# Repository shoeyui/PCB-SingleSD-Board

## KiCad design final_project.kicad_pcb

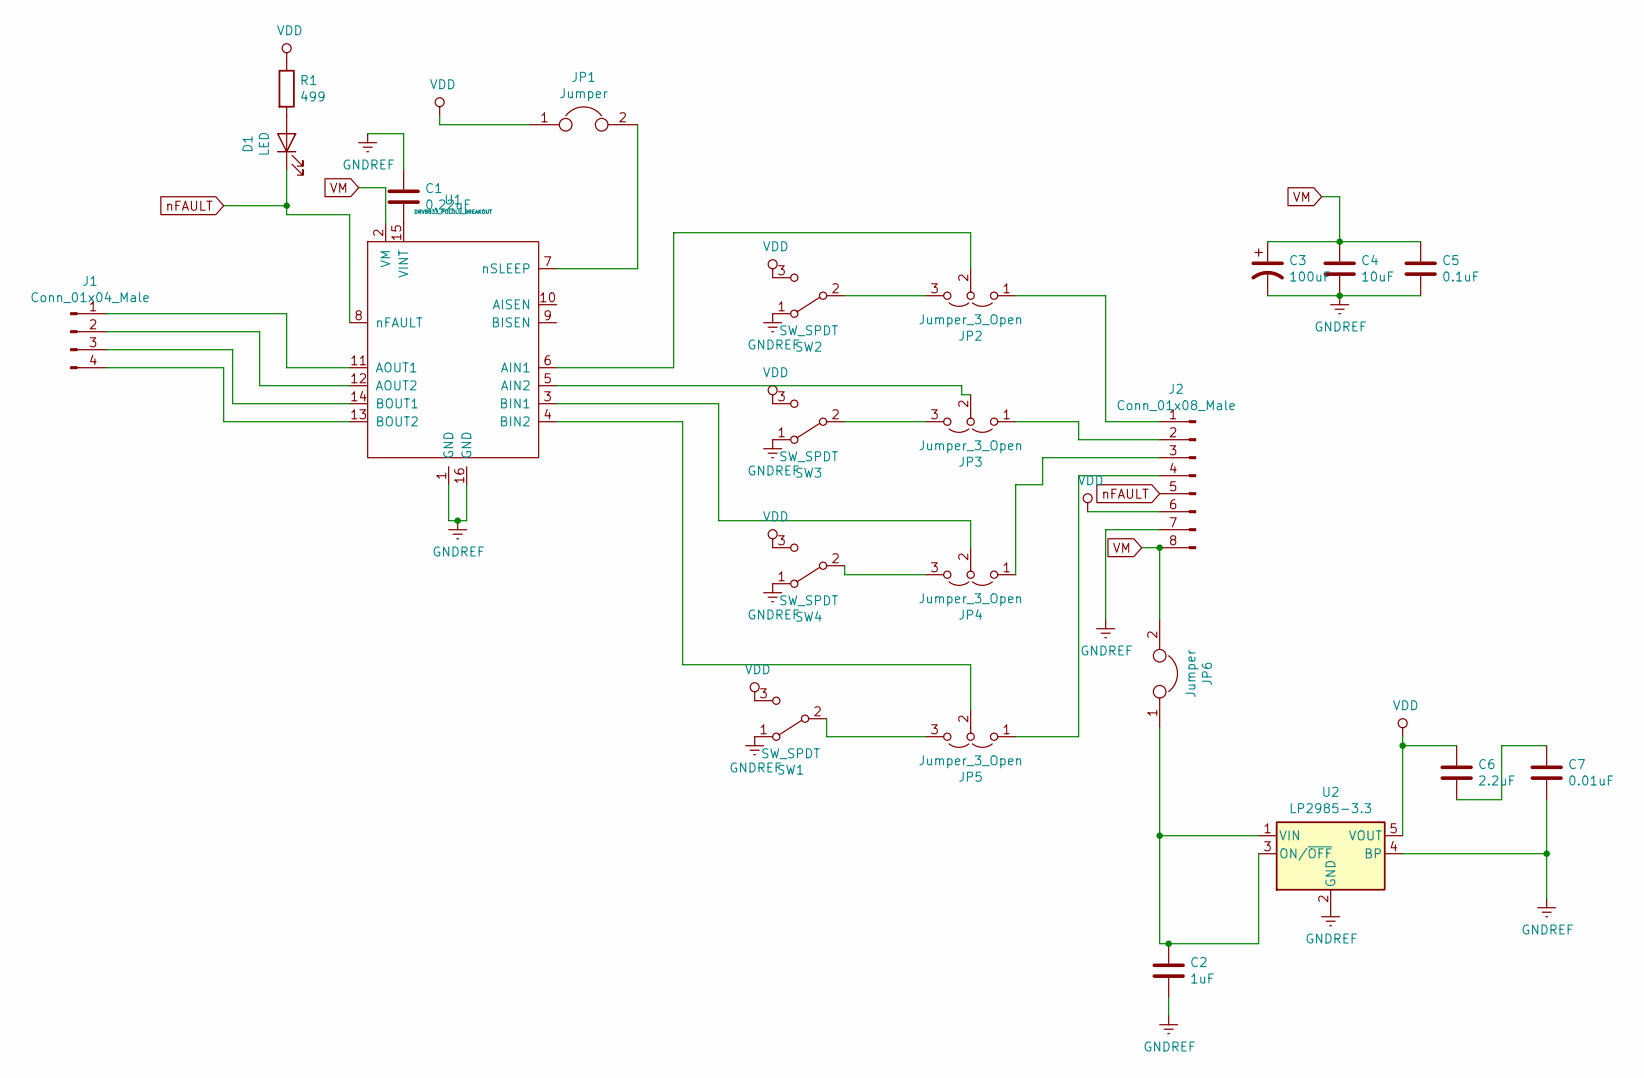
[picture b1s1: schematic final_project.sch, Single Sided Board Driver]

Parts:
C1: 0.22uF; CP_Radial_Tantal_D4.5mm_P2.50mm
C2: 1uF; CP_Radial_D4.0mm_P1.50mm
C3: 100uF; CP_Radial_D8.0mm_P5.00mm
C4: 10uF; CP_Radial_D4.0mm_P1.50mm
C5: 0.1uF; CP_Radial_Tantal_D4.5mm_P2.50mm
C6: 2.2uF; CP_Radial_Tantal_D4.5mm_P2.50mm
C7: 0.01uF; CP_Radial_Tantal_D4.5mm_P2.50mm
D1: LED; LED_D3.0mm
J1: Conn_01x04_Male; PinHeader_1x04_P1.00mm_Vertical
J2: Conn_01x08_Male; PinHeader_1x08_P1.00mm_Vertical
JP1, JP6: Jumper; PinHeader_1x02_P1.00mm_Vertical
JP2, JP3, JP4, JP5: Jumper_3_Open; PinHeader_1x03_P1.00mm_Vertical
R1: 499; R_Axial_DIN0207_L6.3mm_D2.5mm_P7.62mm_Horizontal
SW1, SW2, SW3, SW4: SW_SPDT; SW_CuK_OS102011MA1QN1_SPDT_Angled
U1: DRV8833_POLOLU_BREAKOUT
U2: LP2985-3.3; SOT-23-5

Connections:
GNDREF: C1.1, C2.2, C3.2, C4.2, C5.2, C7.2, J2.7, SW1.1 (A), SW2.1 (A), SW3.1 (A), SW4.1 (A), U1.1 (GND), U1.16 (GND), U2.2 (GND), U2.4 (BP)
unnamed: C1.2, U1.15 (VINT)
unnamed: C2.1, JP6.1, U2.1 (VIN), U2.3 (ON/~OFF~)
unnamed: C6.2, C7.1
unnamed: D1.2 (A), R1.2
unnamed: J1.1, U1.11 (AOUT1)
unnamed: J1.2, U1.12 (AOUT2)
unnamed: J1.3, U1.14 (BOUT1)
unnamed: J1.4, U1.13 (BOUT2)
unnamed: J2.1, JP2.1 (A)
unnamed: J2.2, JP3.1 (A)
unnamed: J2.3, JP4.1 (A)
unnamed: J2.4, JP5.1 (A)
unnamed: JP1.2, U1.7 (nSLEEP)
unnamed: JP2.2 (C), U1.6 (AIN1)
unnamed: JP2.3 (B), SW2.2 (B)
unnamed: JP3.2 (C), U1.5 (AIN2)
unnamed: JP3.3 (B), SW3.2 (B)
unnamed: JP4.2 (C), U1.3 (BIN1)
unnamed: JP4.3 (B), SW4.2 (B)
unnamed: JP5.2 (C), U1.4 (BIN2)
unnamed: JP5.3 (B), SW1.2 (B)
VDD: C6.1, J2.6, JP1.1, R1.1, SW1.3 (C), SW2.3 (C), SW3.3 (C), SW4.3 (C), U2.5 (VOUT)
VM: C3.1, C4.1, C5.1, J2.8, JP6.2, U1.2 (VM)
nFAULT: D1.1 (K), J2.5, U1.8 (nFAULT)

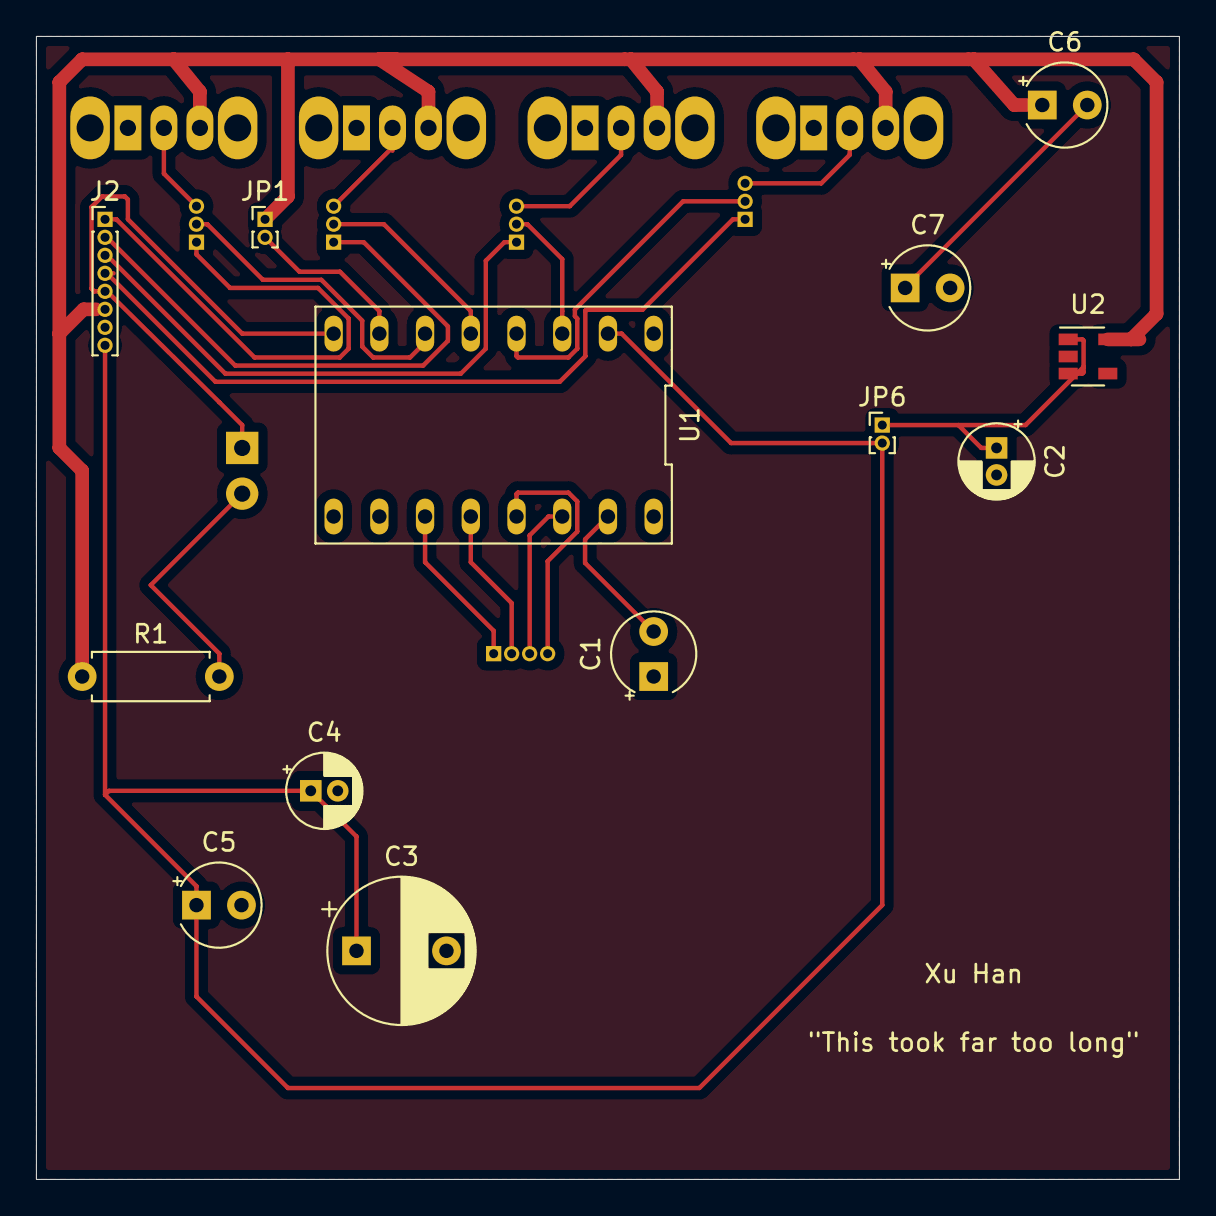
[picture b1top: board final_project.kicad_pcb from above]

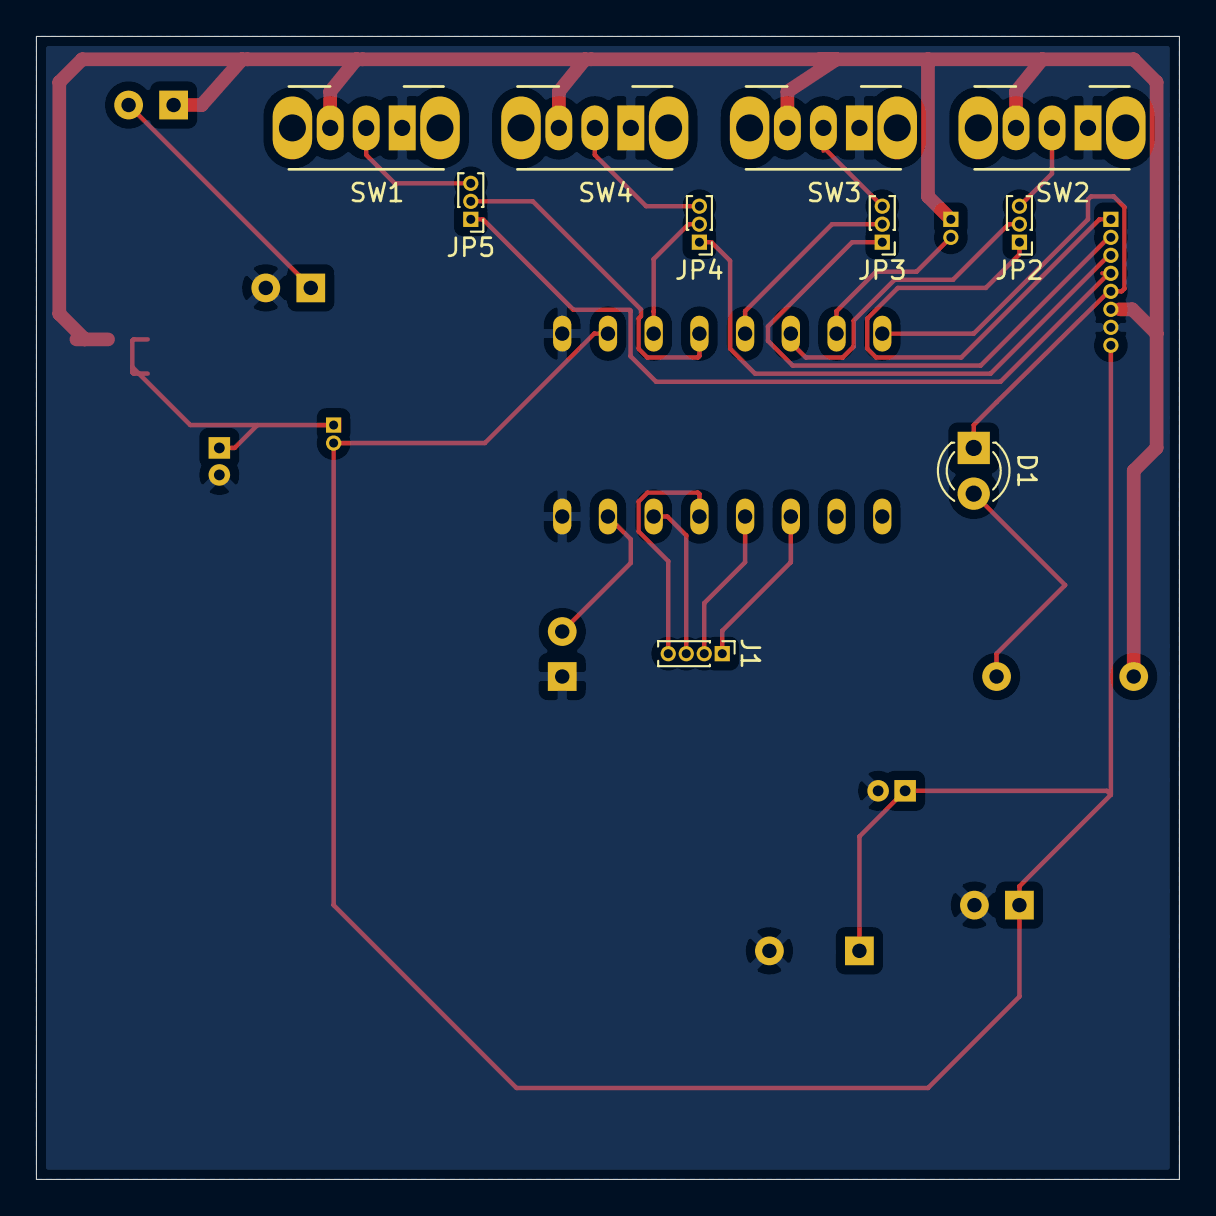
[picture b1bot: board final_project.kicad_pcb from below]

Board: 2 copper layers, 63.5 x 63.5 mm, 23 parts (10 on the bottom side), 25 nets.

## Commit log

2020-08-05 import to github
